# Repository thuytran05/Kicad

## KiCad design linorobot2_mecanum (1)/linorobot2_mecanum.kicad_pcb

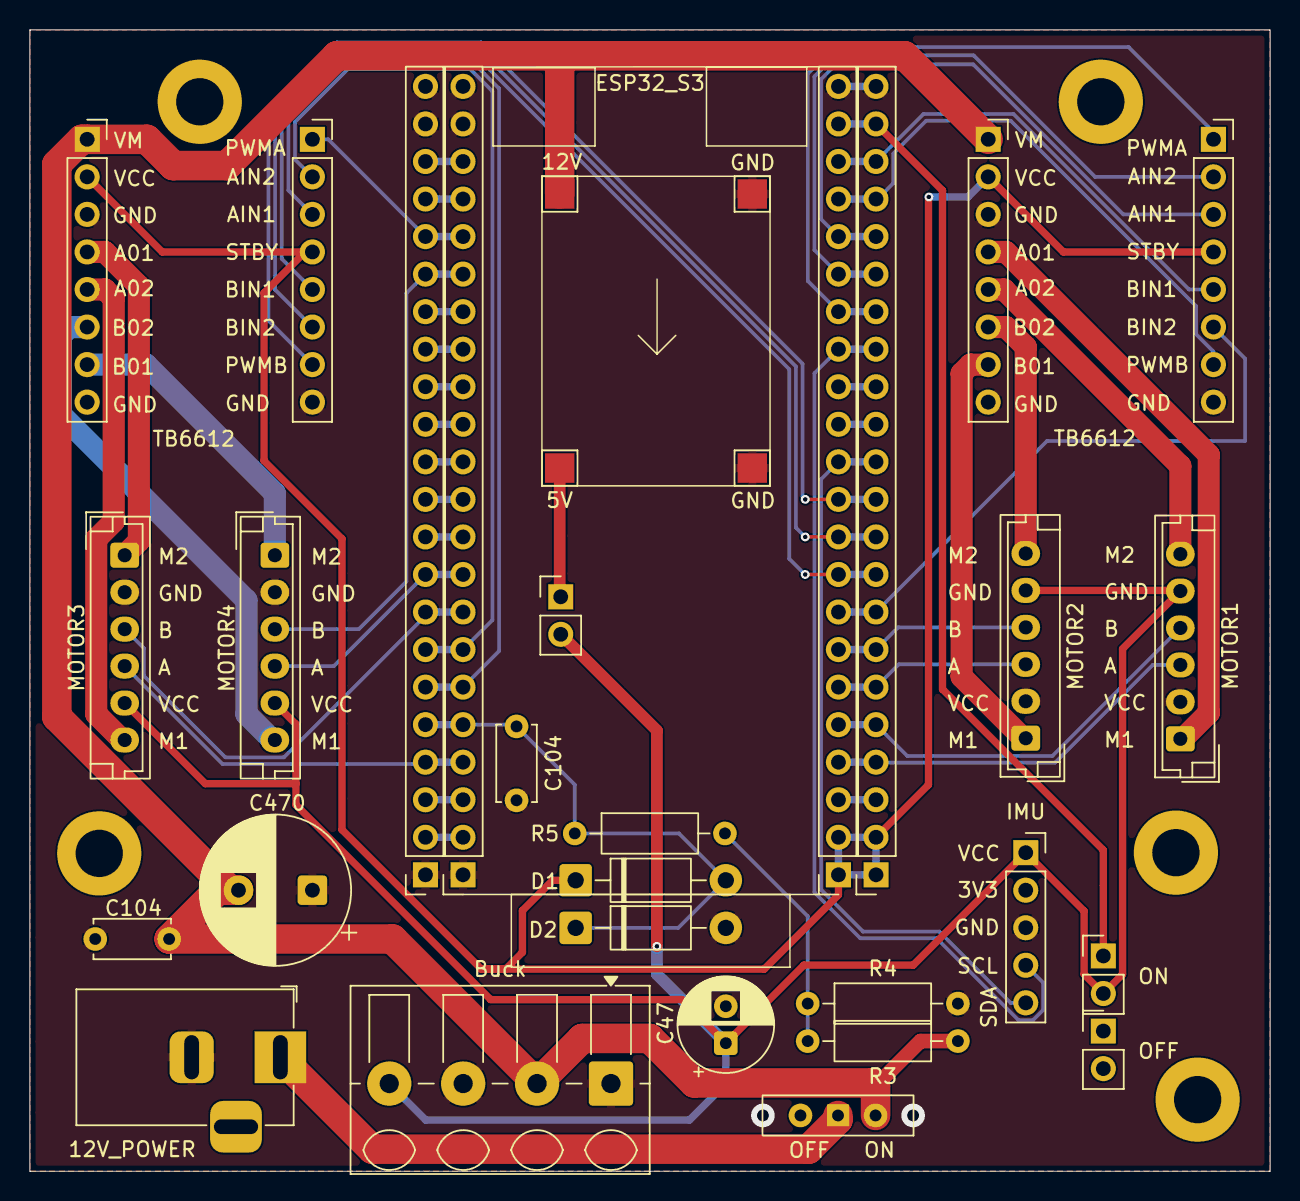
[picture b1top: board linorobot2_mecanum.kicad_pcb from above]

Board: 2 copper layers, 83.9 x 77.2 mm, 32 parts (0 on the bottom side), 53 nets.

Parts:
12V_POWER: Jack-DC; BarrelJack_Horizontal
Buck: Conn_01x04; Altech_AK300_1x04_P5.00mm_45-Degree
C47: C; CP_Radial_D6.3mm_P2.50mm
C104, C104#2: C; C_Disc_D5.0mm_W2.5mm_P5.00mm
C470: C; CP_Radial_D10.0mm_P5.00mm
D1, D2: D_Schottky; D_DO-41_SOD81_P10.16mm_Horizontal
IMU: Conn_01x05_Socket; PinSocket_1x05_P2.54mm_Vertical
J1, J2, J5, J6: Conn_01x08_Socket; PinSocket_1x08_P2.54mm_Vertical
J3, J4, J11: Conn_01x02_Socket; PinHeader_1x02_P2.54mm_Vertical
J7, J8, J9, J10: Conn_01x22_Socket; PinSocket_1x22_P2.54mm_Vertical
MOTOR1, MOTOR2, MOTOR3, MOTOR4: Conn_01x06_Socket; JST_EH_B6B-EH-A_1x06_P2.50mm_Vertical
R3, R4, R5: R; R_Axial_DIN0207_L6.3mm_D2.5mm_P10.16mm_Horizontal
SW1: SW_SPST; SW_Slide-03_Wuerth-WS-SLTV_10x2.5x6.4_P2.54mm
TP1, TP2, TP3, TP4: TestPoint; TestPoint_Pad_2.0x2.0mm

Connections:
3V3: D1.1 (K), J1.2, J2.4, J5.2, J6.4, J7.1, J7.2, J9.1, J9.2
5V: Buck.4, C47.1, IMU.1, J3.2, J11.2, MOTOR1.5, MOTOR2.5, MOTOR3.5, MOTOR4.5
12V: Buck.2, C104#2.1, C470.2, J1.1, J5.1, R3.1, SW1.2 (B), TP1.1 (1_1)
/5V_test: J3.1, J7.21, J9.21
/GPIO0: J8.14, J10.14
/GPIO2: C104.1, D1.2 (A), D2.1 (K), J8.5, J10.5, R5.1
/GPIO3: J7.13, J9.13
/GPIO19: J8.20, J10.20
/GPIO20: J8.19, J10.19
/GPIO35: J8.13, J10.13
/GPIO36: J8.12, J10.12
/GPIO37: J8.11, J10.11
/GPIO38: J8.10, J10.10
/GPIO45: J8.15, J10.15
/GPIO46: J7.14, J9.14
/GPIO48: J8.16, J10.16
/RST: J7.3, J9.3
/RX0: J8.3, J10.3
/TX0: J8.2, J10.2
A01: J1.4, MOTOR1.1
A02: J1.5, MOTOR1.6
A03: J5.4, MOTOR3.1
A04: J5.5, MOTOR3.6
B01: J1.7, MOTOR2.1
B02: J1.6, MOTOR2.6
B03: J5.7, MOTOR4.1
B04: J5.6, MOTOR4.6
GND: 12V_POWER.2, Buck.1, Buck.3, C47.2, C104.2, C104#2.2, C470.1, D2.2 (A), IMU.3, J1.3, J1.8, J2.8, J5.3, J5.8, J6.8, J7.22, J8.1, J8.21, J8.22, J9.22, J10.1, J10.21, J10.22, MOTOR1.2, MOTOR2.2, MOTOR3.2, MOTOR4.2, R4.2, TP2.1 (1_1), TP4.1 (1_1)
MOTOR1_ENCODER_A: J7.5, J9.5, MOTOR1.4
MOTOR1_ENCODER_B: J7.4, J9.4, MOTOR1.3
MOTOR1_IN_A: J2.3, J7.18, J9.18
MOTOR1_IN_B‎: J2.2, J7.17, J9.17
MOTOR1_PWM: J2.1, J7.16, J9.16
MOTOR2_ENCODER_A: J7.7, J9.7, MOTOR2.4
MOTOR2_ENCODER_B: J7.6, J9.6, MOTOR2.3
MOTOR2_IN_A: J2.5, J7.20, J9.20
MOTOR2_IN_B: J2.6, J7.8, J9.8
MOTOR2_PWM‎: J2.7, J7.19, J9.19
MOTOR3_ENCODER_A: J8.4, J10.4, MOTOR3.4
MOTOR3_ENCODER_B: J8.8, J10.8, MOTOR3.3
MOTOR3_IN_A: J6.3, J8.6, J10.6
MOTOR3_IN_B‎: J6.2, J8.7, J10.7
MOTOR3_PWM: J6.1, J8.18, J10.18
MOTOR4_ENCODER_A: J8.9, J10.9, MOTOR4.4
MOTOR4_ENCODER_B: J8.17, J10.17, MOTOR4.3
MOTOR4_IN_A: J6.5, J7.9, J9.9
MOTOR4_IN_B: J6.6, J7.10, J9.10
MOTOR4_PWM‎: J6.7, J7.11, J9.11
unnamed: J11.1, TP3.1 (1_1)
unnamed: R3.2, R4.1, R5.2
unnamed: 12V_POWER.1, SW1.1 (A)
SCL_IMU: IMU.4, J7.15, J9.15
SDA_IMU: IMU.5, J7.12, J9.12

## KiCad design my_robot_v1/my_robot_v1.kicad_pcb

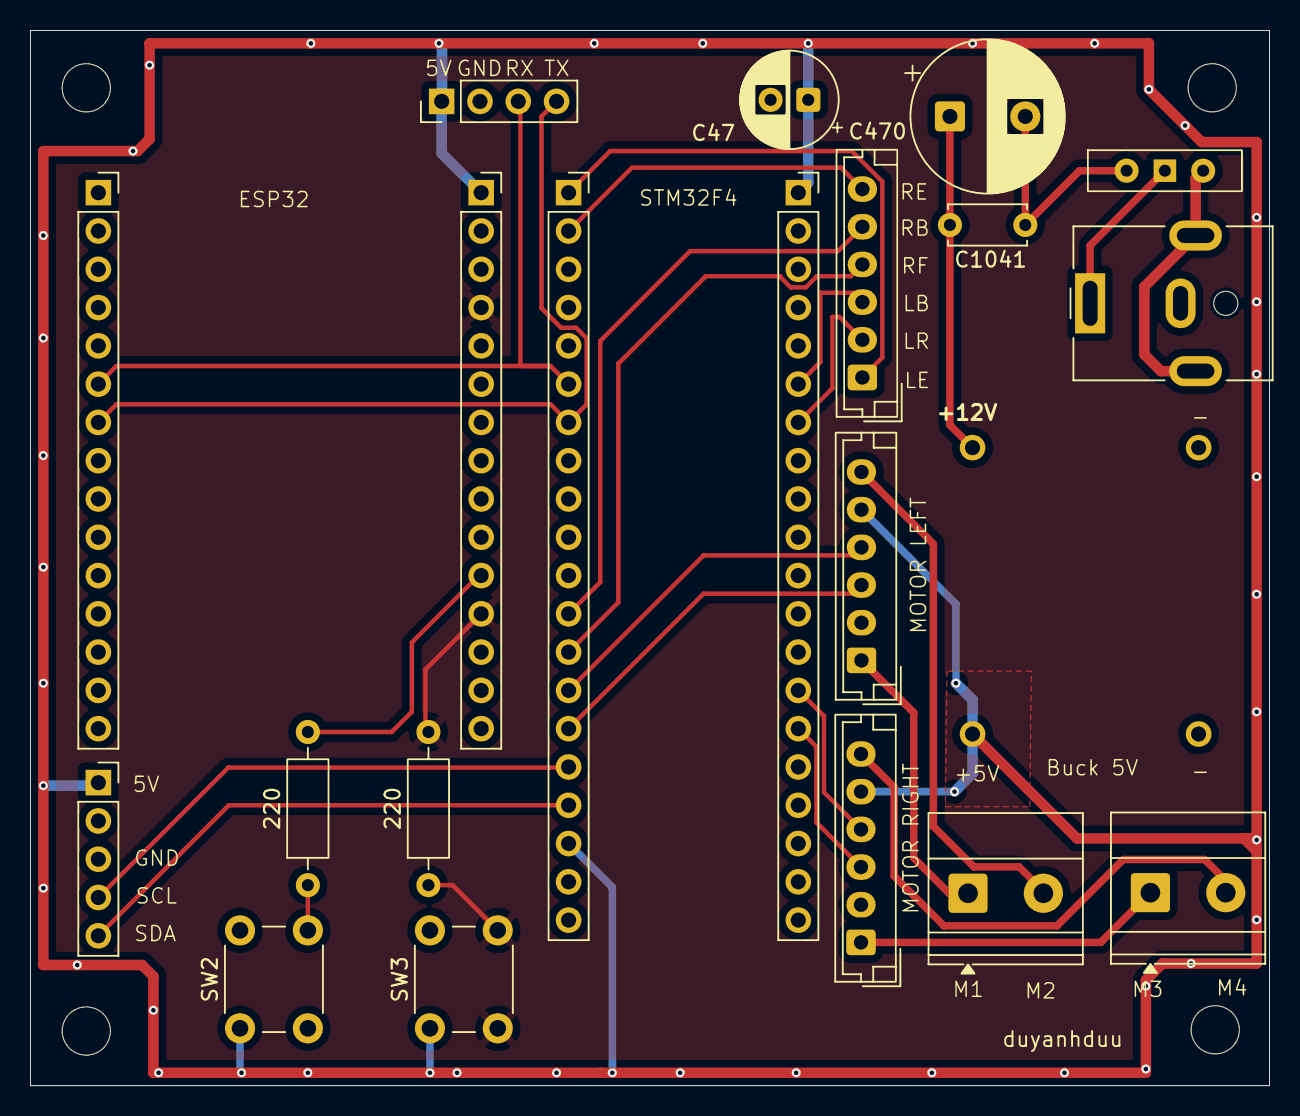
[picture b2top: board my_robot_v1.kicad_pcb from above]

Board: 2 copper layers, 82.2 x 70.0 mm, 21 parts (0 on the bottom side), 25 nets.

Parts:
12V_POWER1: Jack-DC; BarrelJack_CUI_PJ-063AH_Horizontal
220, 220#2: R; R_Axial_DIN0207_L6.3mm_D2.5mm_P10.16mm_Horizontal
Buck1: Conn_01x04; test1
C47: C; CP_Radial_D6.3mm_P2.50mm
C470: C; CP_Radial_D10.0mm_P5.00mm
C1041: C; C_Disc_D5.0mm_W2.5mm_P5.00mm
Debug: Conn_01x04; PinHeader_1x04_P2.54mm_Vertical
ESP32_PIN1, ESP32_PIN2: Conn_01x15_Socket; PinSocket_1x15_P2.54mm_Vertical
IMU1: Conn_01x05_Socket; PinSocket_1x05_P2.54mm_Vertical
L298N_INPUT1: Conn_01x06_Socket; JST_EH_B6B-EH-A_1x06_P2.50mm_Vertical
LEFT_MOTOR1: Conn_01x06_Socket; JST_EH_B6B-EH-A_1x06_P2.50mm_Vertical
ML1: Conn_01x02; TerminalBlock_Phoenix_MKDS-1,5-2_1x02_P5.00mm_Horizontal
MR1: Conn_01x02; TerminalBlock_Phoenix_MKDS-1,5-2_1x02_P5.00mm_Horizontal
RIGHT_MOTOR1: Conn_01x06_Socket; JST_EH_B6B-EH-A_1x06_P2.50mm_Vertical
STM32_PIN1, STM32_PIN2: Conn_01x20_Socket; PinSocket_1x20_P2.54mm_Vertical
SW1: SW_SPST; SW_Slide-03_Wuerth-WS-SLTV_10x2.5x6.4_P2.54mm
SW2, SW3: SW_Push; SW_PUSH_6mm_H5mm

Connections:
3V3: ESP32_PIN1.1, IMU1.2, STM32_PIN1.20, STM32_PIN2.3
5V: Buck1.4, C47.1, Debug.1, ESP32_PIN2.1, IMU1.1, LEFT_MOTOR1.5, RIGHT_MOTOR1.5, STM32_PIN1.18, STM32_PIN2.1, SW2.1, SW3.1
12V: Buck1.2, C470.1, C470.2, C1041.1, C1041.2, SW1.2 (B)
C1: LEFT_MOTOR1.4, STM32_PIN1.14
C2: LEFT_MOTOR1.3, STM32_PIN1.15
C3: RIGHT_MOTOR1.4, STM32_PIN2.14
C4: RIGHT_MOTOR1.3, STM32_PIN2.15
D12: 220.2, ESP32_PIN2.4, ESP32_PIN2.12, SW3.2
D13: 220#2.2, ESP32_PIN2.3, ESP32_PIN2.11, SW2.2
GND: 12V_POWER1.2, 220.1, 220#2.1, Buck1.1, Buck1.3, C47.2, Debug.2, ESP32_PIN1.2, ESP32_PIN2.2, IMU1.3, LEFT_MOTOR1.2, RIGHT_MOTOR1.2, STM32_PIN1.19, STM32_PIN2.2
L_BACK: L298N_INPUT1.3, STM32_PIN2.6
L_FORW: L298N_INPUT1.2, STM32_PIN2.7
L_enablePin: L298N_INPUT1.1, STM32_PIN1.1
M1: LEFT_MOTOR1.1, ML1.1
M2: LEFT_MOTOR1.6, ML1.2
M3: MR1.1, RIGHT_MOTOR1.1
M4: MR1.2, RIGHT_MOTOR1.6
unnamed: 12V_POWER1.1, SW1.1 (A)
RX_PIN: Debug.3, ESP32_PIN1.6, STM32_PIN1.6
R_BACK: L298N_INPUT1.5, STM32_PIN1.12
R_FORW: L298N_INPUT1.4, STM32_PIN1.13
R_enablePin: L298N_INPUT1.6, STM32_PIN1.2
SCL: IMU1.4, STM32_PIN1.16
SDA: IMU1.5, STM32_PIN1.17
TX_PIN: Debug.4, ESP32_PIN1.7, STM32_PIN1.7
